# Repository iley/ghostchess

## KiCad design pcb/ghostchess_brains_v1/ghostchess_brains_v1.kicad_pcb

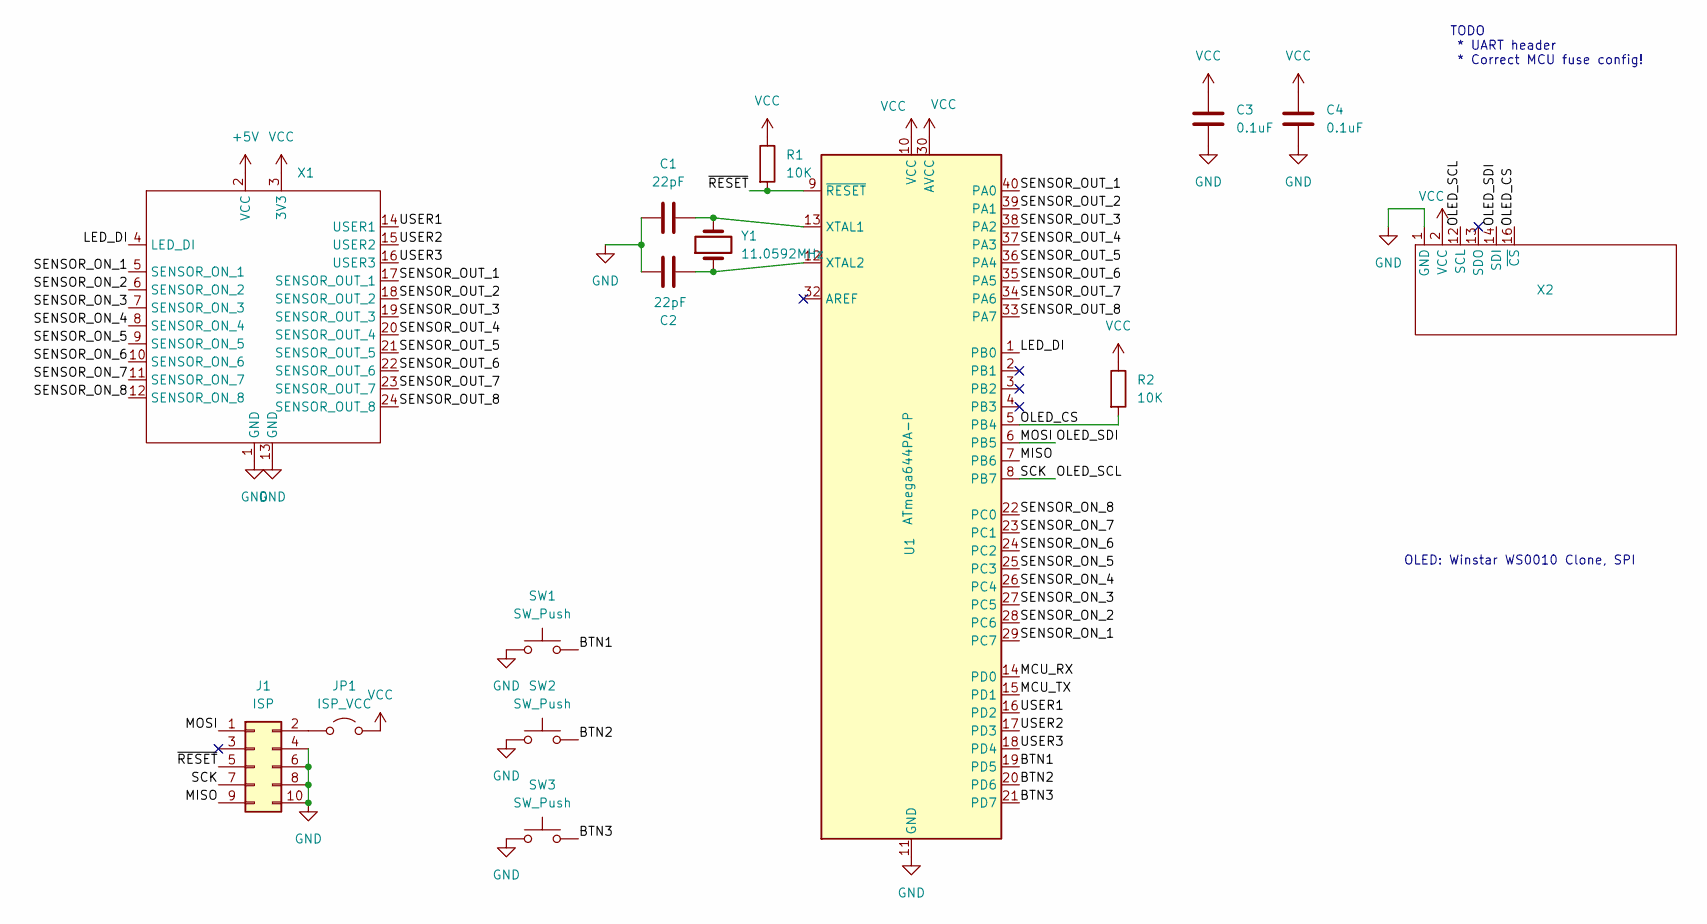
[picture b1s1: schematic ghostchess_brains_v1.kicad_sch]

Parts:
C1, C2: 22pF; C_1206_3216Metric_Pad1.33x1.80mm_HandSolder
C3, C4: 0.1uF; C_1206_3216Metric_Pad1.33x1.80mm_HandSolder
J1: ISP; IDC-Header_2x05_P2.54mm_Horizontal
JP1: ISP_VCC; PinHeader_1x02_P2.54mm_Vertical
R1, R2: 10K; C_1206_3216Metric_Pad1.33x1.80mm_HandSolder
SW1, SW2, SW3: SW_Push; SW_PUSH-12mm
U1: ATmega644PA-P; DIP-40_W15.24mm
X1: GhostChess_Daughter_Board
X2: WC1602A_3Hole
Y1: 11.0592MHz; Crystal_HC49-U_Vertical

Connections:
+5V: X1.2 (VCC)
/BTN1: SW1.2, U1.19 (PD5)
/BTN2: SW2.2, U1.20 (PD6)
/BTN3: SW3.2, U1.21 (PD7)
/LED_DI: U1.1 (PB0), X1.4 (LED_DI)
/MCU_RX: U1.14 (PD0)
/MCU_TX: U1.15 (PD1)
/MISO: J1.9, U1.7 (PB6)
/MOSI: J1.1, U1.6 (PB5), X2.14 (SDI)
/OLED_CS: R2.2, U1.5 (PB4), X2.16 (~CS)
/OLED_SCL: J1.7, U1.8 (PB7), X2.12 (SCL)
/SENSOR_ON_1: U1.29 (PC7), X1.5 (SENSOR_ON_1)
/SENSOR_ON_2: U1.28 (PC6), X1.6 (SENSOR_ON_2)
/SENSOR_ON_3: U1.27 (PC5), X1.7 (SENSOR_ON_3)
/SENSOR_ON_4: U1.26 (PC4), X1.8 (SENSOR_ON_4)
/SENSOR_ON_5: U1.25 (PC3), X1.9 (SENSOR_ON_5)
/SENSOR_ON_6: U1.24 (PC2), X1.10 (SENSOR_ON_6)
/SENSOR_ON_7: U1.23 (PC1), X1.11 (SENSOR_ON_7)
/SENSOR_ON_8: U1.22 (PC0), X1.12 (SENSOR_ON_8)
/SENSOR_OUT_1: U1.40 (PA0), X1.17 (SENSOR_OUT_1)
/SENSOR_OUT_2: U1.39 (PA1), X1.18 (SENSOR_OUT_2)
/SENSOR_OUT_3: U1.38 (PA2), X1.19 (SENSOR_OUT_3)
/SENSOR_OUT_4: U1.37 (PA3), X1.20 (SENSOR_OUT_4)
/SENSOR_OUT_5: U1.36 (PA4), X1.21 (SENSOR_OUT_5)
/SENSOR_OUT_6: U1.35 (PA5), X1.22 (SENSOR_OUT_6)
/SENSOR_OUT_7: U1.34 (PA6), X1.23 (SENSOR_OUT_7)
/SENSOR_OUT_8: U1.33 (PA7), X1.24 (SENSOR_OUT_8)
/USER1: U1.16 (PD2), X1.14 (USER1)
/USER2: U1.17 (PD3), X1.15 (USER2)
/USER3: U1.18 (PD4), X1.16 (USER3)
/~RESET: J1.5, R1.2, U1.9 (~RESET)
GND: C1.1, C2.1, C3.2, C4.2, J1.4, J1.6, J1.8, J1.10, SW1.1, SW2.1, SW3.1, U1.11 (GND), U1.31 (GND), X1.1 (GND), X1.13 (GND), X2.1 (GND)
unnamed: J1.2, JP1.1 (A)
unnamed: C1.2, U1.13 (XTAL1), Y1.2
unnamed: C2.2, U1.12 (XTAL2), Y1.1
VCC: C3.1, C4.1, JP1.2 (B), R1.1, R2.1, U1.10 (VCC), U1.30 (AVCC), X1.3 (3V3), X2.2 (VCC)

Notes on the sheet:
OLED: Winstar WS0010 Clone, SPI
TODO * UART header * Correct MCU fuse config!

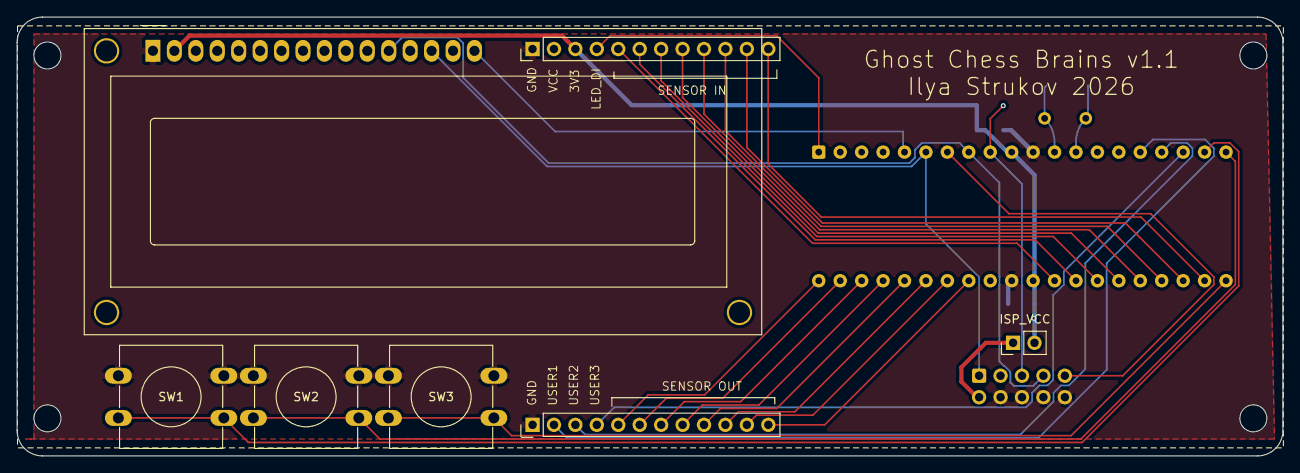
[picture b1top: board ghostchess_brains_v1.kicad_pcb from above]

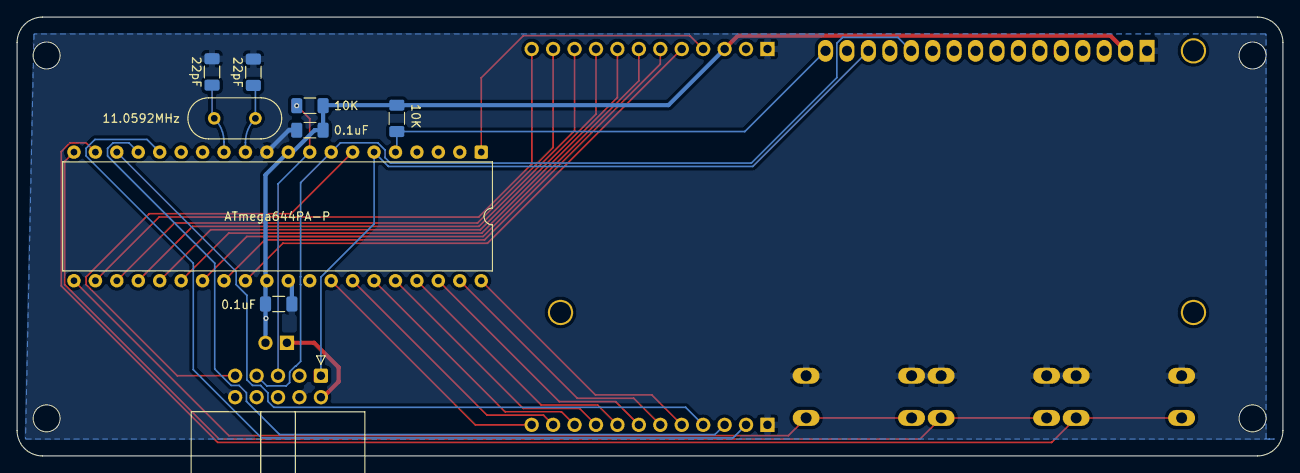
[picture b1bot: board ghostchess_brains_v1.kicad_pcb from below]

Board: 2 copper layers, 150.0 x 52.0 mm, 15 parts (9 on the bottom side), 33 nets.

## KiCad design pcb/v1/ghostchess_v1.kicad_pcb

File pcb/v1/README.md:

# Ghost Chess v1 PCB

## Spreadsheets

Use https://github.com/TheJigsApp/kicad-parts-placer-pcm

Run `./convert-spreadsheet.sh watch`

Edit `kicadpartsplacer-report.ods` in LibreOffice.

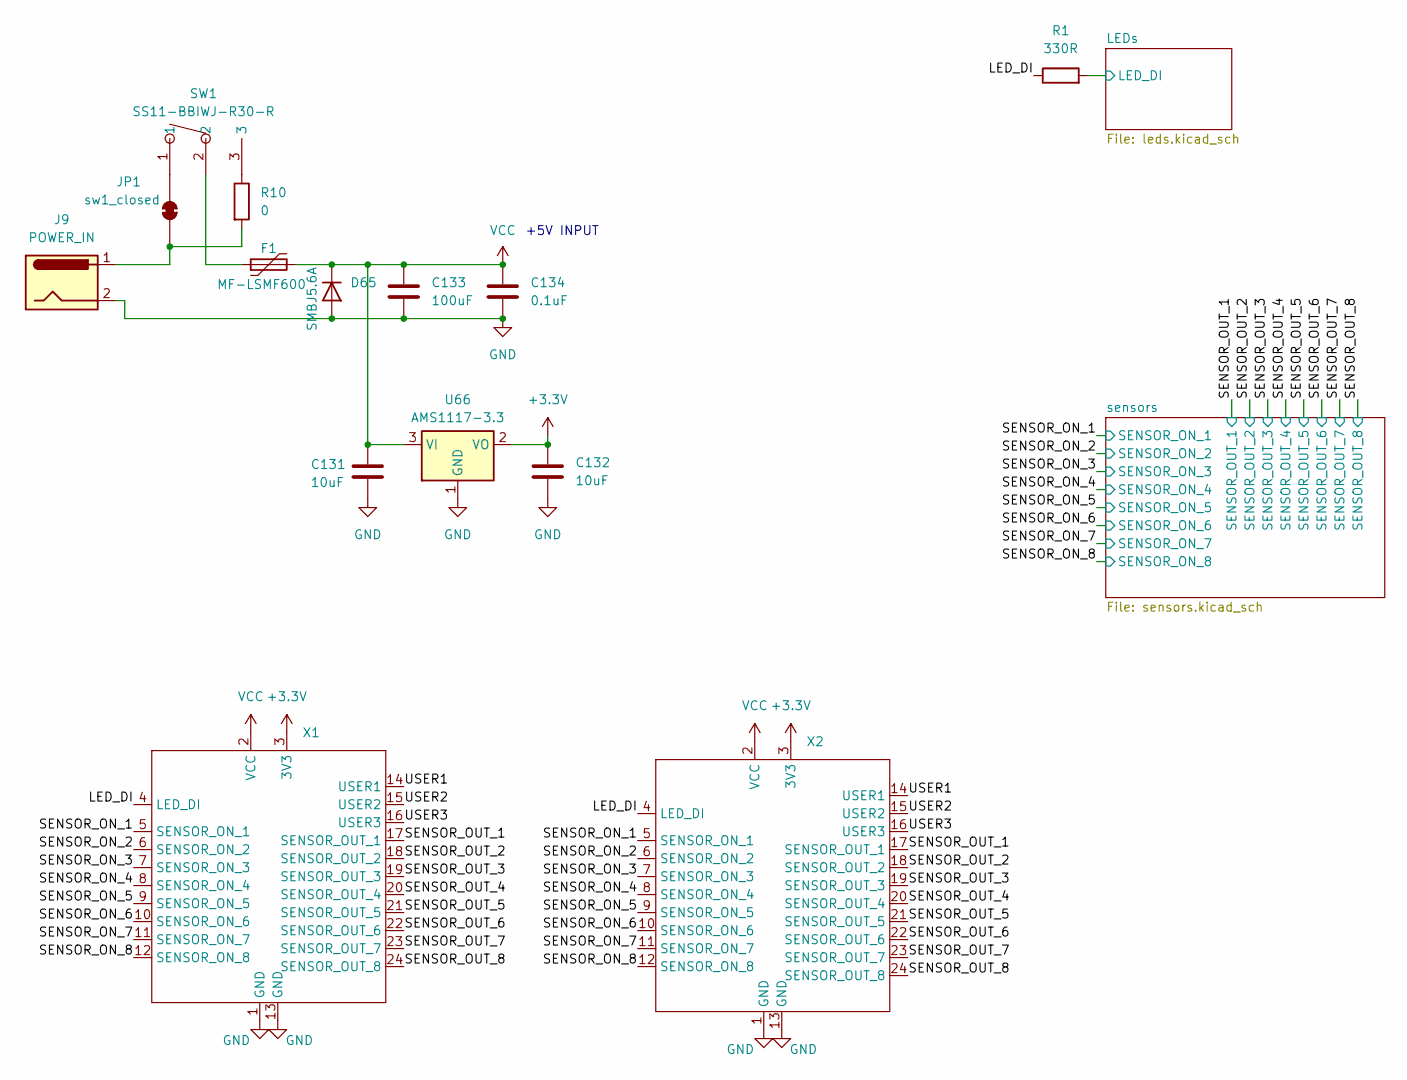
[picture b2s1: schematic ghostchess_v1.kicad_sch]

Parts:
C131, C132: 10uF; C_1206_3216Metric_Pad1.33x1.80mm_HandSolder
C133: 100uF; C_1206_3216Metric_Pad1.33x1.80mm_HandSolder
C134: 0.1uF; C_1206_3216Metric_Pad1.33x1.80mm_HandSolder
D65: SMBJ5.6A; D_SMB_Handsoldering
F1: MF-LSMF600; Fuse_2920_7451Metric_Pad2.10x5.45mm_HandSolder
J9: POWER_IN; BarrelJack_Horizontal
JP1: sw1_closed; SolderJumper-2_P1.3mm_Bridged_Pad1.0x1.5mm
R1: 330R; R_1206_3216Metric_Pad1.30x1.75mm_HandSolder
R10: 0; R_1206_3216Metric_Pad1.30x1.75mm_HandSolder
SW1: SS11-BBIWJ-R30-R; SW-TH_SS11-BBIWJ-R30-R; LCSC Part C309071
U66: AMS1117-3.3; SOT-223-3_TabPin2
X1, X2: GhostChess_Daughter_Board

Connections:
+3.3V: C132.1, U66.2 (VO), X1.3 (3V3), X2.3 (3V3); also elsewhere on the board
/LED_DI: R1.1, X1.4 (LED_DI), X2.4 (LED_DI)
/LEDs/LED_DI: R1.2; also elsewhere on the board
/SENSOR_ON_1: X1.5 (SENSOR_ON_1), X2.5 (SENSOR_ON_1); also elsewhere on the board
/SENSOR_ON_2: X1.6 (SENSOR_ON_2), X2.6 (SENSOR_ON_2); also elsewhere on the board
/SENSOR_ON_3: X1.7 (SENSOR_ON_3), X2.7 (SENSOR_ON_3); also elsewhere on the board
/SENSOR_ON_4: X1.8 (SENSOR_ON_4), X2.8 (SENSOR_ON_4); also elsewhere on the board
/SENSOR_ON_5: X1.9 (SENSOR_ON_5), X2.9 (SENSOR_ON_5); also elsewhere on the board
/SENSOR_ON_6: X1.10 (SENSOR_ON_6), X2.10 (SENSOR_ON_6); also elsewhere on the board
/SENSOR_ON_7: X1.11 (SENSOR_ON_7), X2.11 (SENSOR_ON_7); also elsewhere on the board
/SENSOR_ON_8: X1.12 (SENSOR_ON_8), X2.12 (SENSOR_ON_8); also elsewhere on the board
/SENSOR_OUT_1: X1.17 (SENSOR_OUT_1), X2.17 (SENSOR_OUT_1); also elsewhere on the board
/SENSOR_OUT_2: X1.18 (SENSOR_OUT_2), X2.18 (SENSOR_OUT_2); also elsewhere on the board
/SENSOR_OUT_3: X1.19 (SENSOR_OUT_3), X2.19 (SENSOR_OUT_3); also elsewhere on the board
/SENSOR_OUT_4: X1.20 (SENSOR_OUT_4), X2.20 (SENSOR_OUT_4); also elsewhere on the board
/SENSOR_OUT_5: X1.21 (SENSOR_OUT_5), X2.21 (SENSOR_OUT_5); also elsewhere on the board
/SENSOR_OUT_6: X1.22 (SENSOR_OUT_6), X2.22 (SENSOR_OUT_6); also elsewhere on the board
/SENSOR_OUT_7: X1.23 (SENSOR_OUT_7), X2.23 (SENSOR_OUT_7); also elsewhere on the board
/SENSOR_OUT_8: X1.24 (SENSOR_OUT_8), X2.24 (SENSOR_OUT_8); also elsewhere on the board
/USER1: X1.14 (USER1), X2.14 (USER1)
/USER2: X1.15 (USER2), X2.15 (USER2)
/USER3: X1.16 (USER3), X2.16 (USER3)
GND: C131.2, C132.2, C133.2, C134.2, D65.2 (A), J9.2, U66.1 (GND), X1.1 (GND), X1.13 (GND), X2.1 (GND), X2.13 (GND); also elsewhere on the board
unnamed: F1.1, SW1.2
unnamed: J9.1, JP1.1 (A), R10.2
unnamed: JP1.2 (B), SW1.1
unnamed: R10.1, SW1.3
VCC: C131.1, C133.1, C134.1, D65.1 (K), F1.2, U66.3 (VI), X1.2 (VCC), X2.2 (VCC); also elsewhere on the board

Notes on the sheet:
+5V INPUT

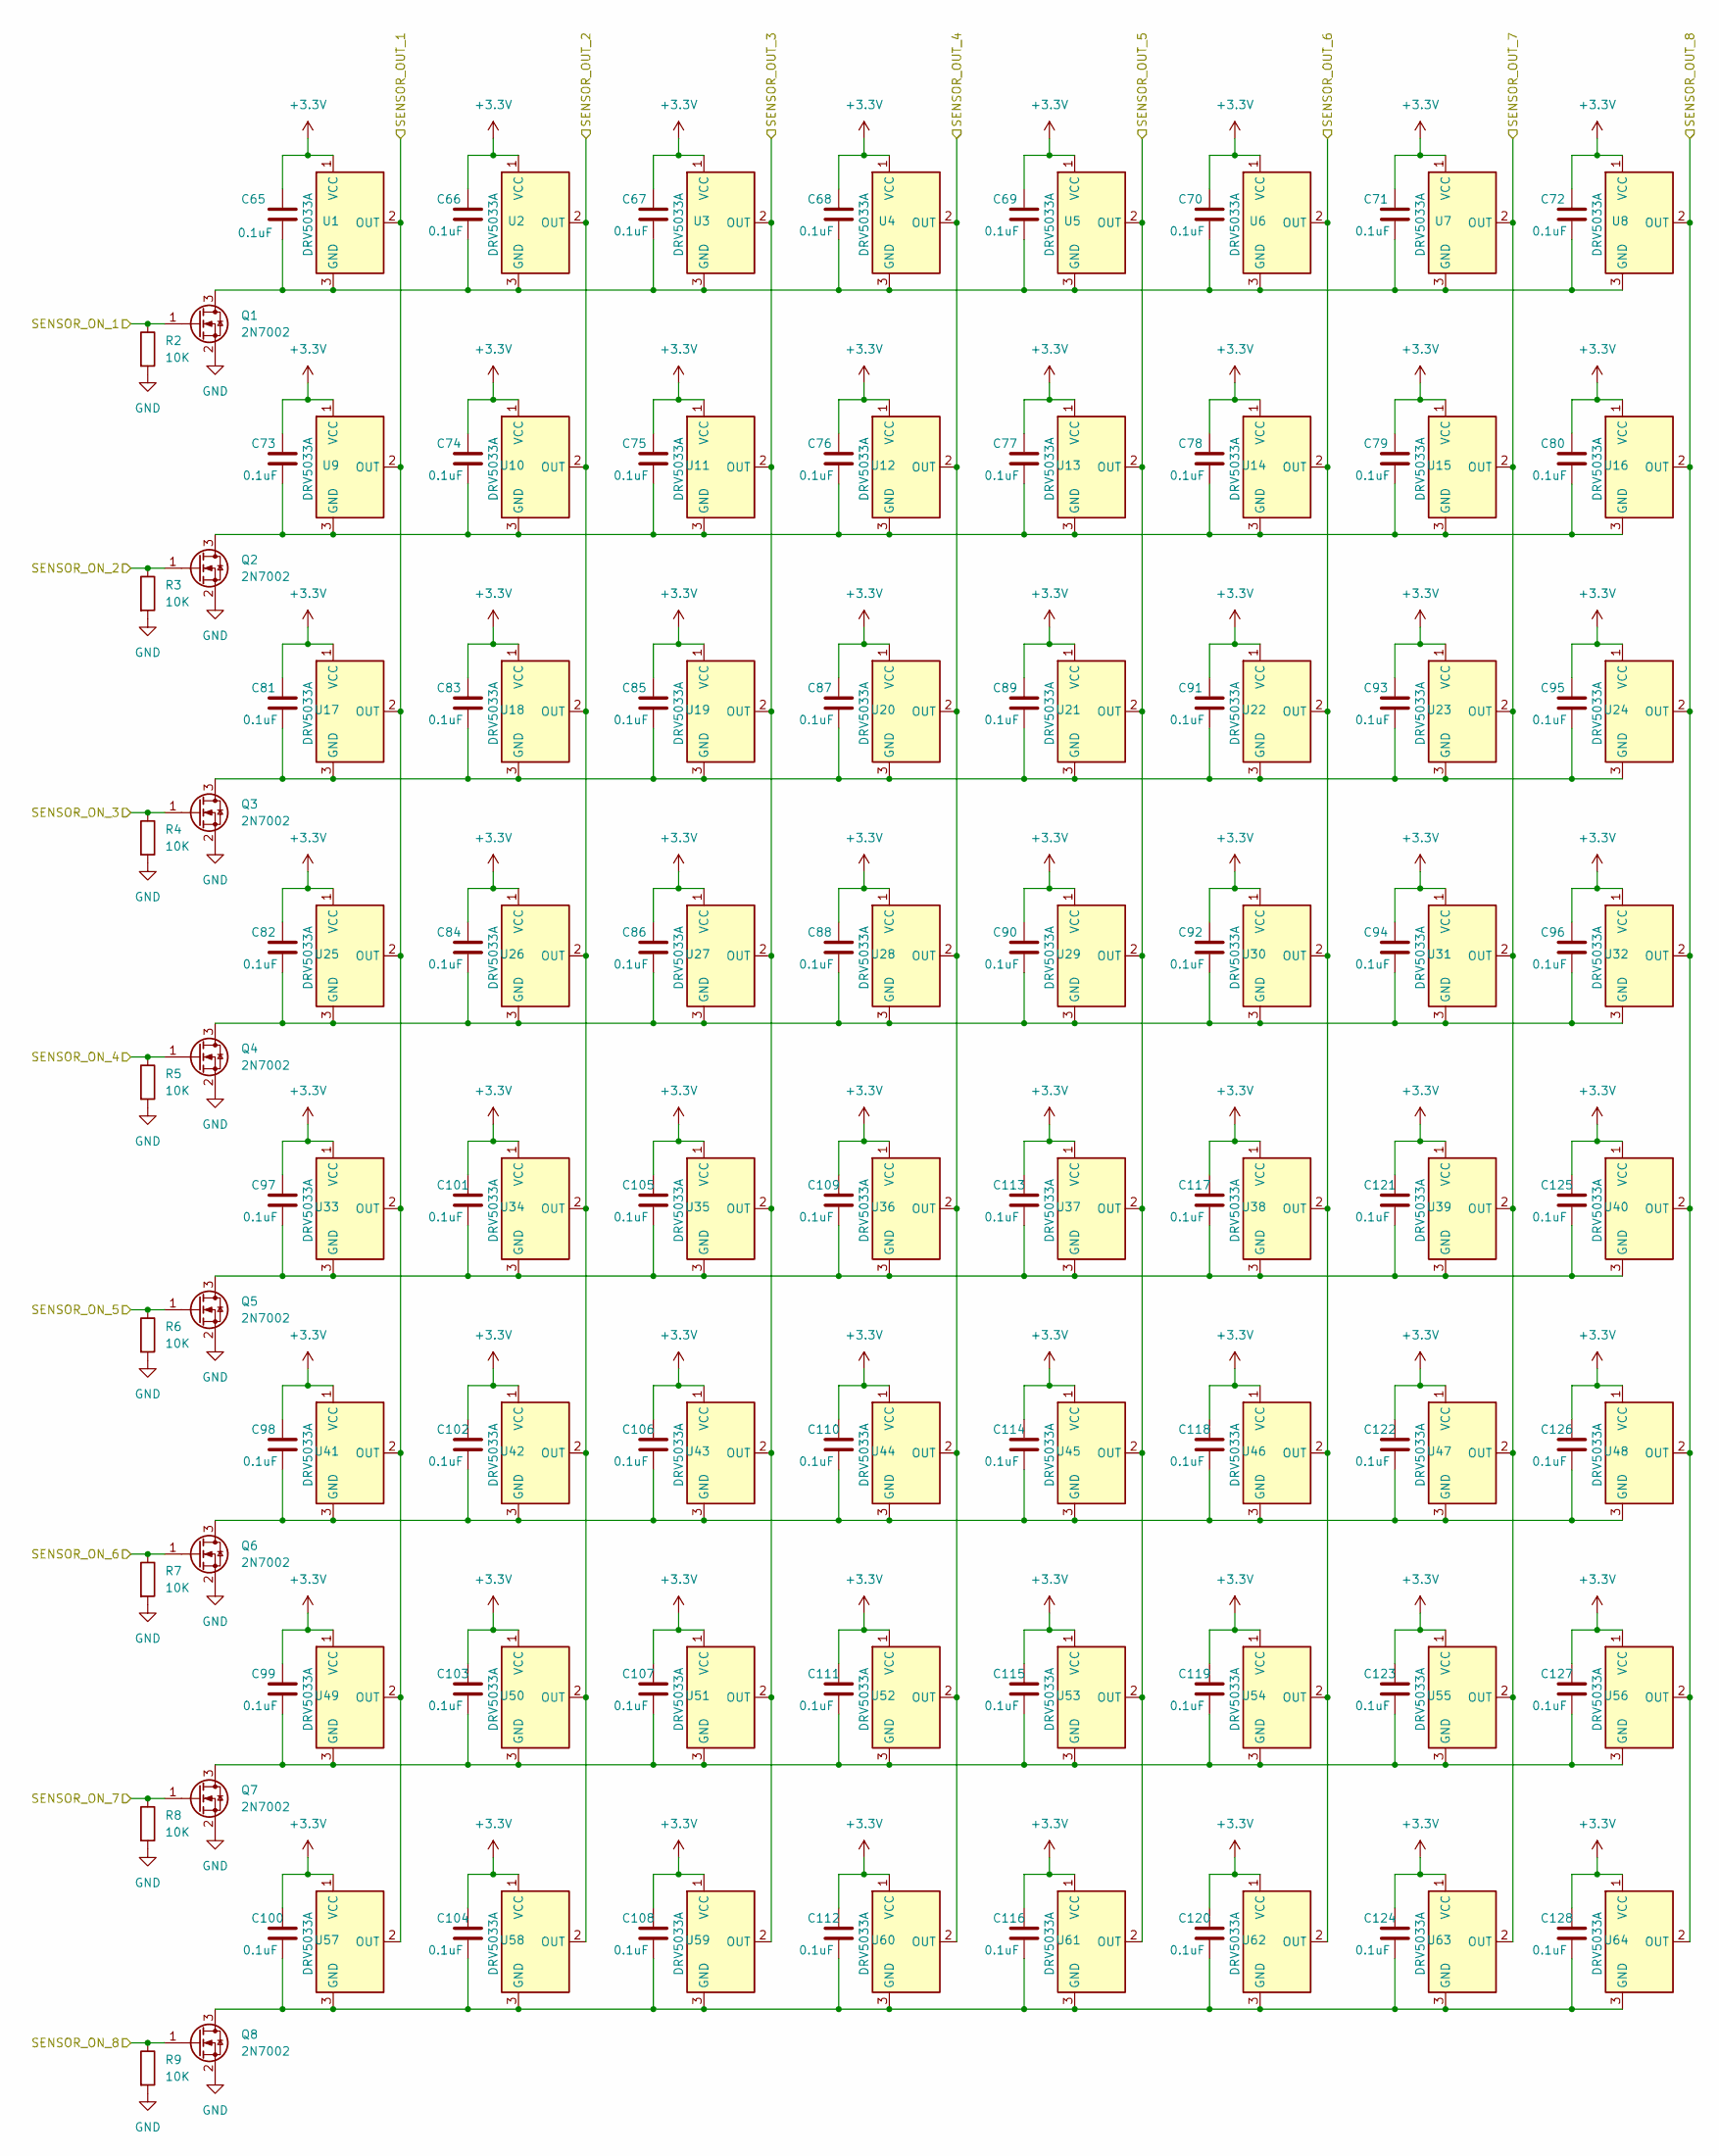
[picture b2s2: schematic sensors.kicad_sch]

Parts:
C65, C66, C67, C68, C69, C70, C71, C72, C73, C74, C75, C76, C77, C78, C79, C80, C81, C82, C83, C84, C85, C86, C87, C88, C89, C90, C91, C92, C93, C94, C95, C96, C97, C98, C99, C100, C101, C102, C103, C104, C105, C106, C107, C108, C109, C110, C111, C112, C113, C114, C115, C116, C117, C118, C119, C120, C121, C122, C123, C124, C125, C126, C127, C128: 0.1uF; C_1206_3216Metric_Pad1.33x1.80mm_HandSolder
Q1, Q2, Q3, Q4, Q5, Q6, Q7, Q8: 2N7002; SOT-23
R2, R3, R4, R5, R6, R7, R8, R9: 10K; R_1206_3216Metric_Pad1.30x1.75mm_HandSolder
U1, U2, U3, U4, U5, U6, U7, U8, U9, U10, U11, U12, U13, U14, U15, U16, U17, U18, U19, U20, U21, U22, U23, U24, U25, U26, U27, U28, U29, U30, U31, U32, U33, U34, U35, U36, U37, U38, U39, U40, U41, U42, U43, U44, U45, U46, U47, U48, U49, U50, U51, U52, U53, U54, U55, U56, U57, U58, U59, U60, U61, U62, U63, U64: DRV5033A; SOT-23

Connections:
+3.3V: C65.2, C66.1, C67.1, C68.1, C69.1, C70.1, C71.1, C72.1, C73.1, C74.1, C75.1, C76.1, C77.1, C78.1, C79.1, C80.1, C81.1, C82.1, C83.1, C84.1, C85.1, C86.1, C87.1, C88.1, C89.1, C90.1, C91.1, C92.1, C93.1, C94.1, C95.1, C96.1, C97.1, C98.1, C99.1, C100.1, C101.1, C102.1, C103.1, C104.1, C105.1, C106.1, C107.1, C108.1, C109.1, C110.1, C111.1, C112.1, C113.1, C114.1, C115.1, C116.1, C117.1, C118.1, C119.1, C120.1, C121.1, C122.1, C123.1, C124.1, C125.1, C126.1, C127.1, C128.1, U1.1 (VCC), U2.1 (VCC), U3.1 (VCC), U4.1 (VCC), U5.1 (VCC), U6.1 (VCC), U7.1 (VCC), U8.1 (VCC), U9.1 (VCC), U10.1 (VCC), U11.1 (VCC), U12.1 (VCC), U13.1 (VCC), U14.1 (VCC), U15.1 (VCC), U16.1 (VCC), U17.1 (VCC), U18.1 (VCC), U19.1 (VCC), U20.1 (VCC), U21.1 (VCC), U22.1 (VCC), U23.1 (VCC), U24.1 (VCC), U25.1 (VCC), U26.1 (VCC), U27.1 (VCC), U28.1 (VCC), U29.1 (VCC), U30.1 (VCC), U31.1 (VCC), U32.1 (VCC), U33.1 (VCC), U34.1 (VCC), U35.1 (VCC), U36.1 (VCC), U37.1 (VCC), U38.1 (VCC), U39.1 (VCC), U40.1 (VCC), U41.1 (VCC), U42.1 (VCC), U43.1 (VCC), U44.1 (VCC), U45.1 (VCC), U46.1 (VCC), U47.1 (VCC), U48.1 (VCC), U49.1 (VCC), U50.1 (VCC), U51.1 (VCC), U52.1 (VCC), U53.1 (VCC), U54.1 (VCC), U55.1 (VCC), U56.1 (VCC), U57.1 (VCC), U58.1 (VCC), U59.1 (VCC), U60.1 (VCC), U61.1 (VCC), U62.1 (VCC), U63.1 (VCC), U64.1 (VCC); also elsewhere on the board
/SENSOR_ON_1: Q1.1 (G), R2.1; also elsewhere on the board
/SENSOR_ON_2: Q2.1 (G), R3.1; also elsewhere on the board
/SENSOR_ON_3: Q3.1 (G), R4.1; also elsewhere on the board
/SENSOR_ON_4: Q4.1 (G), R5.1; also elsewhere on the board
/SENSOR_ON_5: Q5.1 (G), R6.1; also elsewhere on the board
/SENSOR_ON_6: Q6.1 (G), R7.1; also elsewhere on the board
/SENSOR_ON_7: Q7.1 (G), R8.1; also elsewhere on the board
/SENSOR_ON_8: Q8.1 (G), R9.1; also elsewhere on the board
/SENSOR_OUT_1: U1.2 (OUT), U9.2 (OUT), U17.2 (OUT), U25.2 (OUT), U33.2 (OUT), U41.2 (OUT), U49.2 (OUT), U57.2 (OUT); also elsewhere on the board
/SENSOR_OUT_2: U2.2 (OUT), U10.2 (OUT), U18.2 (OUT), U26.2 (OUT), U34.2 (OUT), U42.2 (OUT), U50.2 (OUT), U58.2 (OUT); also elsewhere on the board
/SENSOR_OUT_3: U3.2 (OUT), U11.2 (OUT), U19.2 (OUT), U27.2 (OUT), U35.2 (OUT), U43.2 (OUT), U51.2 (OUT), U59.2 (OUT); also elsewhere on the board
/SENSOR_OUT_4: U4.2 (OUT), U12.2 (OUT), U20.2 (OUT), U28.2 (OUT), U36.2 (OUT), U44.2 (OUT), U52.2 (OUT), U60.2 (OUT); also elsewhere on the board
/SENSOR_OUT_5: U5.2 (OUT), U13.2 (OUT), U21.2 (OUT), U29.2 (OUT), U37.2 (OUT), U45.2 (OUT), U53.2 (OUT), U61.2 (OUT); also elsewhere on the board
/SENSOR_OUT_6: U6.2 (OUT), U14.2 (OUT), U22.2 (OUT), U30.2 (OUT), U38.2 (OUT), U46.2 (OUT), U54.2 (OUT), U62.2 (OUT); also elsewhere on the board
/SENSOR_OUT_7: U7.2 (OUT), U15.2 (OUT), U23.2 (OUT), U31.2 (OUT), U39.2 (OUT), U47.2 (OUT), U55.2 (OUT), U63.2 (OUT); also elsewhere on the board
/SENSOR_OUT_8: U8.2 (OUT), U16.2 (OUT), U24.2 (OUT), U32.2 (OUT), U40.2 (OUT), U48.2 (OUT), U56.2 (OUT), U64.2 (OUT); also elsewhere on the board
GND: Q1.2 (S), Q2.2 (S), Q3.2 (S), Q4.2 (S), Q5.2 (S), Q6.2 (S), Q7.2 (S), Q8.2 (S), R2.2, R3.2, R4.2, R5.2, R6.2, R7.2, R8.2, R9.2; also elsewhere on the board
unnamed: C65.1, C66.2, C67.2, C68.2, C69.2, C70.2, C71.2, C72.2, Q1.3 (D), U1.3 (GND), U2.3 (GND), U3.3 (GND), U4.3 (GND), U5.3 (GND), U6.3 (GND), U7.3 (GND), U8.3 (GND)
unnamed: C73.2, C74.2, C75.2, C76.2, C77.2, C78.2, C79.2, C80.2, Q2.3 (D), U9.3 (GND), U10.3 (GND), U11.3 (GND), U12.3 (GND), U13.3 (GND), U14.3 (GND), U15.3 (GND), U16.3 (GND)
unnamed: C81.2, C83.2, C85.2, C87.2, C89.2, C91.2, C93.2, C95.2, Q3.3 (D), U17.3 (GND), U18.3 (GND), U19.3 (GND), U20.3 (GND), U21.3 (GND), U22.3 (GND), U23.3 (GND), U24.3 (GND)
unnamed: C82.2, C84.2, C86.2, C88.2, C90.2, C92.2, C94.2, C96.2, Q4.3 (D), U25.3 (GND), U26.3 (GND), U27.3 (GND), U28.3 (GND), U29.3 (GND), U30.3 (GND), U31.3 (GND), U32.3 (GND)
unnamed: C97.2, C101.2, C105.2, C109.2, C113.2, C117.2, C121.2, C125.2, Q5.3 (D), U33.3 (GND), U34.3 (GND), U35.3 (GND), U36.3 (GND), U37.3 (GND), U38.3 (GND), U39.3 (GND), U40.3 (GND)
unnamed: C98.2, C102.2, C106.2, C110.2, C114.2, C118.2, C122.2, C126.2, Q6.3 (D), U41.3 (GND), U42.3 (GND), U43.3 (GND), U44.3 (GND), U45.3 (GND), U46.3 (GND), U47.3 (GND), U48.3 (GND)
unnamed: C99.2, C103.2, C107.2, C111.2, C115.2, C119.2, C123.2, C127.2, Q7.3 (D), U49.3 (GND), U50.3 (GND), U51.3 (GND), U52.3 (GND), U53.3 (GND), U54.3 (GND), U55.3 (GND), U56.3 (GND)
unnamed: C100.2, C104.2, C108.2, C112.2, C116.2, C120.2, C124.2, C128.2, Q8.3 (D), U57.3 (GND), U58.3 (GND), U59.3 (GND), U60.3 (GND), U61.3 (GND), U62.3 (GND), U63.3 (GND), U64.3 (GND)

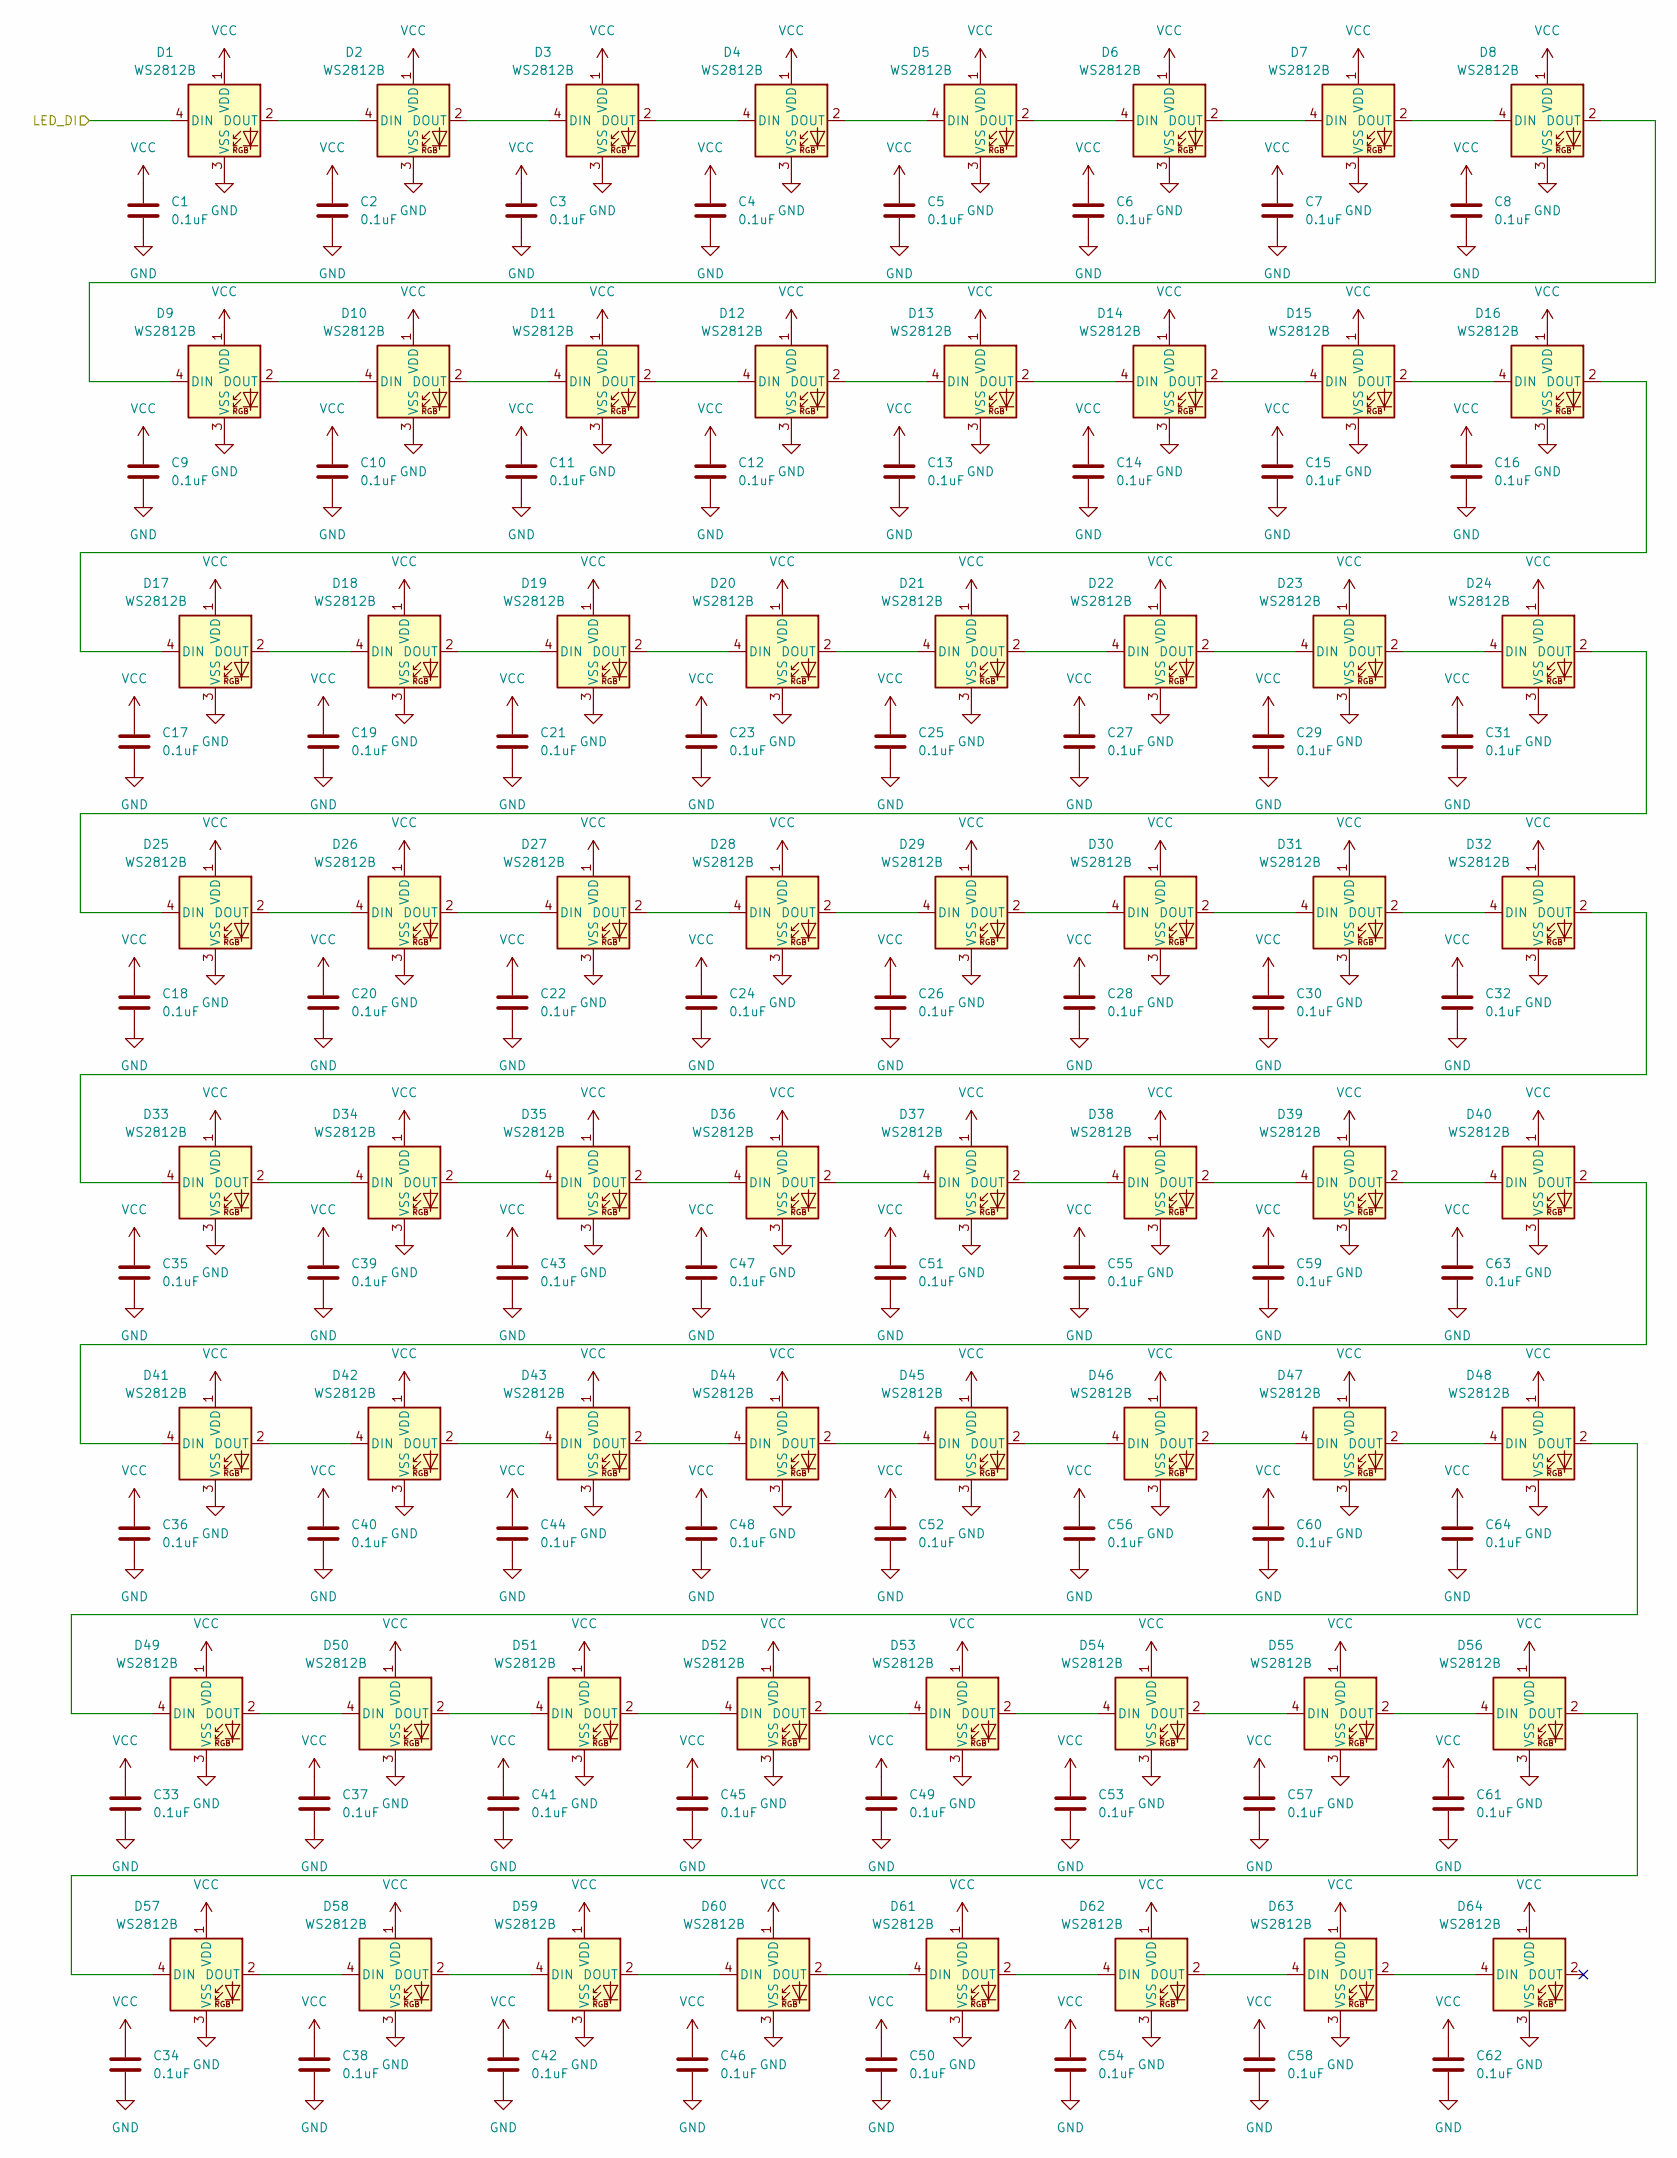
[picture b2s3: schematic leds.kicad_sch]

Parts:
C1, C2, C3, C4, C5, C6, C7, C8, C9, C10, C11, C12, C13, C14, C15, C16, C17, C18, C19, C20, C21, C22, C23, C24, C25, C26, C27, C28, C29, C30, C31, C32, C33, C34, C35, C36, C37, C38, C39, C40, C41, C42, C43, C44, C45, C46, C47, C48, C49, C50, C51, C52, C53, C54, C55, C56, C57, C58, C59, C60, C61, C62, C63, C64: 0.1uF; C_1206_3216Metric_Pad1.33x1.80mm_HandSolder
D1, D2, D3, D4, D5, D6, D7, D8, D9, D10, D11, D12, D13, D14, D15, D16, D17, D18, D19, D20, D21, D22, D23, D24, D25, D26, D27, D28, D29, D30, D31, D32, D33, D34, D35, D36, D37, D38, D39, D40, D41, D42, D43, D44, D45, D46, D47, D48, D49, D50, D51, D52, D53, D54, D55, D56, D57, D58, D59, D60, D61, D62, D63, D64: WS2812B; LED_WS2812B_PLCC4_5.0x5.0mm_P3.2mm

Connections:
/LEDs/LED_DI: D1.4 (DIN); also elsewhere on the board
GND: C1.2, C2.2, C3.2, C4.2, C5.2, C6.2, C7.2, C8.2, C9.2, C10.2, C11.2, C12.2, C13.2, C14.2, C15.2, C16.2, C17.2, C18.2, C19.2, C20.2, C21.2, C22.2, C23.2, C24.2, C25.2, C26.2, C27.2, C28.2, C29.2, C30.2, C31.2, C32.2, C33.2, C34.2, C35.2, C36.2, C37.2, C38.2, C39.2, C40.2, C41.2, C42.2, C43.2, C44.2, C45.2, C46.2, C47.2, C48.2, C49.2, C50.2, C51.2, C52.2, C53.2, C54.2, C55.2, C56.2, C57.2, C58.2, C59.2, C60.2, C61.2, C62.2, C63.2, C64.2, D1.3 (VSS), D2.3 (VSS), D3.3 (VSS), D4.3 (VSS), D5.3 (VSS), D6.3 (VSS), D7.3 (VSS), D8.3 (VSS), D9.3 (VSS), D10.3 (VSS), D11.3 (VSS), D12.3 (VSS), D13.3 (VSS), D14.3 (VSS), D15.3 (VSS), D16.3 (VSS), D17.3 (VSS), D18.3 (VSS), D19.3 (VSS), D20.3 (VSS), D21.3 (VSS), D22.3 (VSS), D23.3 (VSS), D24.3 (VSS), D25.3 (VSS), D26.3 (VSS), D27.3 (VSS), D28.3 (VSS), D29.3 (VSS), D30.3 (VSS), D31.3 (VSS), D32.3 (VSS), D33.3 (VSS), D34.3 (VSS), D35.3 (VSS), D36.3 (VSS), D37.3 (VSS), D38.3 (VSS), D39.3 (VSS), D40.3 (VSS), D41.3 (VSS), D42.3 (VSS), D43.3 (VSS), D44.3 (VSS), D45.3 (VSS), D46.3 (VSS), D47.3 (VSS), D48.3 (VSS), D49.3 (VSS), D50.3 (VSS), D51.3 (VSS), D52.3 (VSS), D53.3 (VSS), D54.3 (VSS), D55.3 (VSS), D56.3 (VSS), D57.3 (VSS), D58.3 (VSS), D59.3 (VSS), D60.3 (VSS), D61.3 (VSS), D62.3 (VSS), D63.3 (VSS), D64.3 (VSS); also elsewhere on the board
unnamed: D1.2 (DOUT), D2.4 (DIN)
unnamed: D2.2 (DOUT), D3.4 (DIN)
unnamed: D3.2 (DOUT), D4.4 (DIN)
unnamed: D4.2 (DOUT), D5.4 (DIN)
unnamed: D5.2 (DOUT), D6.4 (DIN)
unnamed: D6.2 (DOUT), D7.4 (DIN)
unnamed: D7.2 (DOUT), D8.4 (DIN)
unnamed: D8.2 (DOUT), D9.4 (DIN)
unnamed: D9.2 (DOUT), D10.4 (DIN)
unnamed: D10.2 (DOUT), D11.4 (DIN)
unnamed: D11.2 (DOUT), D12.4 (DIN)
unnamed: D12.2 (DOUT), D13.4 (DIN)
unnamed: D13.2 (DOUT), D14.4 (DIN)
unnamed: D14.2 (DOUT), D15.4 (DIN)
unnamed: D15.2 (DOUT), D16.4 (DIN)
unnamed: D16.2 (DOUT), D17.4 (DIN)
unnamed: D17.2 (DOUT), D18.4 (DIN)
unnamed: D18.2 (DOUT), D19.4 (DIN)
unnamed: D19.2 (DOUT), D20.4 (DIN)
unnamed: D20.2 (DOUT), D21.4 (DIN)
unnamed: D21.2 (DOUT), D22.4 (DIN)
unnamed: D22.2 (DOUT), D23.4 (DIN)
unnamed: D23.2 (DOUT), D24.4 (DIN)
unnamed: D24.2 (DOUT), D25.4 (DIN)
unnamed: D25.2 (DOUT), D26.4 (DIN)
unnamed: D26.2 (DOUT), D27.4 (DIN)
unnamed: D27.2 (DOUT), D28.4 (DIN)
unnamed: D28.2 (DOUT), D29.4 (DIN)
unnamed: D29.2 (DOUT), D30.4 (DIN)
unnamed: D30.2 (DOUT), D31.4 (DIN)
unnamed: D31.2 (DOUT), D32.4 (DIN)
unnamed: D32.2 (DOUT), D33.4 (DIN)
unnamed: D33.2 (DOUT), D34.4 (DIN)
unnamed: D34.2 (DOUT), D35.4 (DIN)
unnamed: D35.2 (DOUT), D36.4 (DIN)
unnamed: D36.2 (DOUT), D37.4 (DIN)
unnamed: D37.2 (DOUT), D38.4 (DIN)
unnamed: D38.2 (DOUT), D39.4 (DIN)
unnamed: D39.2 (DOUT), D40.4 (DIN)
unnamed: D40.2 (DOUT), D41.4 (DIN)
unnamed: D41.2 (DOUT), D42.4 (DIN)
unnamed: D42.2 (DOUT), D43.4 (DIN)
unnamed: D43.2 (DOUT), D44.4 (DIN)
unnamed: D44.2 (DOUT), D45.4 (DIN)
unnamed: D45.2 (DOUT), D46.4 (DIN)
unnamed: D46.2 (DOUT), D47.4 (DIN)
unnamed: D47.2 (DOUT), D48.4 (DIN)
unnamed: D48.2 (DOUT), D49.4 (DIN)
unnamed: D49.2 (DOUT), D50.4 (DIN)
unnamed: D50.2 (DOUT), D51.4 (DIN)
unnamed: D51.2 (DOUT), D52.4 (DIN)
unnamed: D52.2 (DOUT), D53.4 (DIN)
unnamed: D53.2 (DOUT), D54.4 (DIN)
unnamed: D54.2 (DOUT), D55.4 (DIN)
unnamed: D55.2 (DOUT), D56.4 (DIN)
unnamed: D56.2 (DOUT), D57.4 (DIN)
unnamed: D57.2 (DOUT), D58.4 (DIN)
unnamed: D58.2 (DOUT), D59.4 (DIN)
unnamed: D59.2 (DOUT), D60.4 (DIN)
unnamed: D60.2 (DOUT), D61.4 (DIN)
unnamed: D61.2 (DOUT), D62.4 (DIN)
unnamed: D62.2 (DOUT), D63.4 (DIN)
unnamed: D63.2 (DOUT), D64.4 (DIN)
VCC: C1.1, C2.1, C3.1, C4.1, C5.1, C6.1, C7.1, C8.1, C9.1, C10.1, C11.1, C12.1, C13.1, C14.1, C15.1, C16.1, C17.1, C18.1, C19.1, C20.1, C21.1, C22.1, C23.1, C24.1, C25.1, C26.1, C27.1, C28.1, C29.1, C30.1, C31.1, C32.1, C33.1, C34.1, C35.1, C36.1, C37.1, C38.1, C39.1, C40.1, C41.1, C42.1, C43.1, C44.1, C45.1, C46.1, C47.1, C48.1, C49.1, C50.1, C51.1, C52.1, C53.1, C54.1, C55.1, C56.1, C57.1, C58.1, C59.1, C60.1, C61.1, C62.1, C63.1, C64.1, D1.1 (VDD), D2.1 (VDD), D3.1 (VDD), D4.1 (VDD), D5.1 (VDD), D6.1 (VDD), D7.1 (VDD), D8.1 (VDD), D9.1 (VDD), D10.1 (VDD), D11.1 (VDD), D12.1 (VDD), D13.1 (VDD), D14.1 (VDD), D15.1 (VDD), D16.1 (VDD), D17.1 (VDD), D18.1 (VDD), D19.1 (VDD), D20.1 (VDD), D21.1 (VDD), D22.1 (VDD), D23.1 (VDD), D24.1 (VDD), D25.1 (VDD), D26.1 (VDD), D27.1 (VDD), D28.1 (VDD), D29.1 (VDD), D30.1 (VDD), D31.1 (VDD), D32.1 (VDD), D33.1 (VDD), D34.1 (VDD), D35.1 (VDD), D36.1 (VDD), D37.1 (VDD), D38.1 (VDD), D39.1 (VDD), D40.1 (VDD), D41.1 (VDD), D42.1 (VDD), D43.1 (VDD), D44.1 (VDD), D45.1 (VDD), D46.1 (VDD), D47.1 (VDD), D48.1 (VDD), D49.1 (VDD), D50.1 (VDD), D51.1 (VDD), D52.1 (VDD), D53.1 (VDD), D54.1 (VDD), D55.1 (VDD), D56.1 (VDD), D57.1 (VDD), D58.1 (VDD), D59.1 (VDD), D60.1 (VDD), D61.1 (VDD), D62.1 (VDD), D63.1 (VDD), D64.1 (VDD); also elsewhere on the board
